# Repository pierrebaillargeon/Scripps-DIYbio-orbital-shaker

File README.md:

# Scripps-DIYbio-orbital-shaker
 Electronic circuitboard designed for the DIYbio orbital shaker project (https://www.thingiverse.com/thing:2633507).
 
 An assembly guide for this project can be found here: https://scrippsresearch.dozuki.com/Guide/How+to+assemble+a+DIYbio+orbital+shaker/1
 
 All files were generated using KiCad 5. Gerber files necessary to order PCBs can be found in the GERBER-v1.1 subdirectory.
 
  Close up photo of DIYbio orbital shaker PCB v1.1.
 
  Three DIYbio orbital shaker v1.1 PCBs prior to assembly.
 
  Three DIYbio orbital shaker v1.1 PCBs post assembly.
 
 Three DIYbio orbital shaker v1.1 PCBs with all peripheral devices connected.
 
  Photo illustrating DIYbio orbital shaker with custom PCB versus prior version made with protoboard.

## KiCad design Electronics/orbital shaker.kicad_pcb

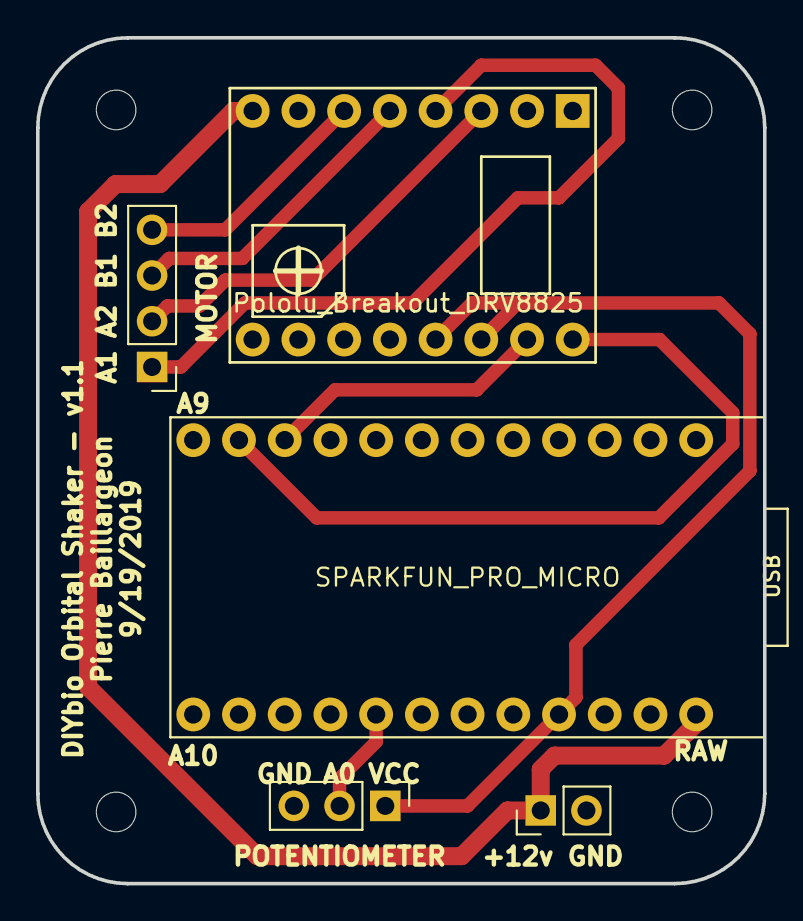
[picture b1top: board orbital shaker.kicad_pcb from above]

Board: 2 copper layers, 40.4 x 47.0 mm, 5 parts (0 on the bottom side), 10 nets.

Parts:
A1: Pololu_Breakout_DRV8825; POLOLU-DRV8825
B1: SPARKFUN_PRO_MICRO
J1: Conn_01x02_Female; Pin_Header_Straight_1x02_Pitch2.54mm
J2: Conn_01x04_Female; Pin_Header_Straight_1x04_Pitch2.54mm
J3: Conn_01x03_Female; Pin_Header_Straight_1x03_Pitch2.54mm

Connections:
+12V: A1.8, B1.24, J1.1
GND: A1.1, A1.7, B1.3, B1.4, B1.23, J1.2, J3.3
unnamed: A1.3, J2.2
unnamed: A1.4, J2.1
unnamed: A1.5, J2.3
unnamed: A1.6, J2.4
unnamed: A1.13, A1.14, B1.21, J3.1
unnamed: A1.15, B1.10
unnamed: A1.16, B1.11
unnamed: B1.17, J3.2

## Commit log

2019-10-23 Added photos of PCB
    Adding photos of PCB before and after assembly in DIYbio orbital shaker.
2019-10-23 Added photos of PCB in various stage of assembly.
2020-01-07 Adding orbital shaker Arduino firmware to repository
2020-01-07 Added link to assembly guide
2020-01-13 Added 3D model files for v1.1
    Includes STL files for 3D printing and .f3z/.f3d files for editing in Fusion 360.
2021-08-13 Updating readme to match new repository name
2021-08-13 Reorganized directory structure
2021-12-03 Reorganized CAD folder and added STEP files
    Exported STEP files for non-Fusion 360 users and organized all CAD files into subfolders.
2021-12-03 CAD folder file name cleanup + added missing components
2021-12-08 Added front PCB copper layer export in SVG
    Added front copper layer design in SVG format for anyone who would like to recreate using a DIY etching technique.
